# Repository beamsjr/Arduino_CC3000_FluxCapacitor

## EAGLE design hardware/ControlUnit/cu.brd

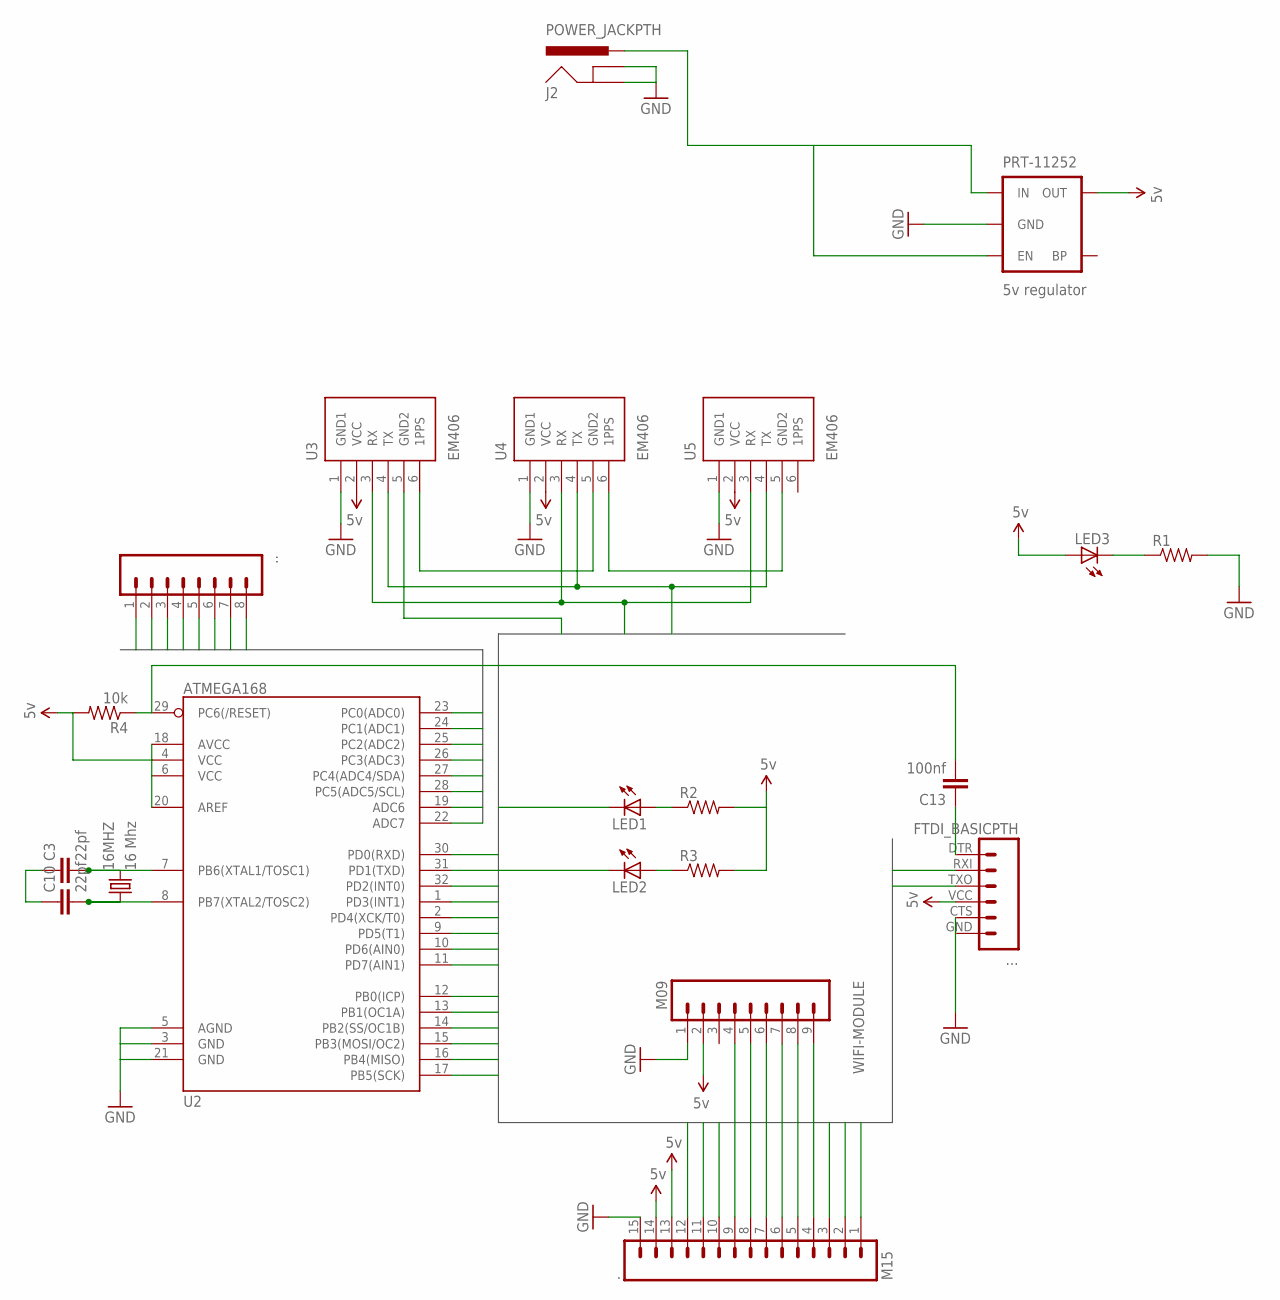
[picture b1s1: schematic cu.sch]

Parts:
16MHZ: 16 Mhz; HC49US
.: M15; 1X15
..: M081X08; 1X08
...: FTDI_BASICPTH; FTDI_BASIC
C3, C10: 22pf; 0805
C13: 100nf; 0805
J2: POWER_JACKPTH; POWER_JACK_PTH
LED1, LED2, LED3: LED1206; LED-1206
PRT-11252: 5v regulator; SOT23-5
R1, R2, R3: RESISTOR0805-RES; 0805
R4: 10k; R0805
U2: ATMEGA168; TQFP32-08
U3, U4, U5: EM406
WIFI-MODULE: M09; 1X09

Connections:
5VCC: ....VCC (4), PRT-11252.5 (OUT), R4.2, U2.4 (VCC), U2.6 (VCC), U2.18 (AVCC), U2.20 (AREF)
A0: ...1, U2.23 (PC0(ADC0))
A1: ...2, U2.24 (PC1(ADC1))
A2: ...3, U2.25 (PC2(ADC2))
A3: ...4, U2.26 (PC3(ADC3))
A4: ...5, U2.27 (PC4(ADC4/SDA))
A5: ...6, U2.28 (PC5(ADC5/SCL))
A6: ...7, U2.19 (ADC6)
A7: ...8, U2.22 (ADC7)
D0: ....TXO (3), LED1.C, U2.30 (PD0(RXD))
D1: ....RXI (2), LED2.C, U2.31 (PD1(TXD))
D2: ..1, U2.32 (PD2(INT0)), WIFI-MODULE.7
D3: ..2, U2.1 (PD3(INT1))
D4: ..3, U2.2 (PD4(XCK/T0))
D5: ..4, U2.9 (PD5(T1)), U3.4 (TX), U4.4 (TX), U5.4 (TX)
D6: ..5, U2.10 (PD6(AIN0)), U3.3 (RX), U4.3 (RX), U5.3 (RX)
D7: ..6, U2.11 (PD7(AIN1)), U3.5 (GND2)
D8: ..7, U2.12 (PB0(ICP))
D9: ..8, U2.13 (PB1(OC1A)), WIFI-MODULE.9
D10: ..9, U2.14 (PB2(SS/OC1B)), WIFI-MODULE.6
D11: ..10, U2.15 (PB3(MOSI/OC2)), WIFI-MODULE.4
D12: ..11, U2.16 (PB4(MISO)), WIFI-MODULE.5
D13: ..12, U2.17 (PB5(SCK)), WIFI-MODULE.8
GND: ..15, ....CTS (5), ....GND (6), J2.GND, J2.GNDBREAK, PRT-11252.2 (GND), R1.2, U2.3 (GND), U2.5 (AGND), U2.21 (GND), U3.1 (GND1), U4.1 (GND1), U5.1 (GND1), WIFI-MODULE.1
unnamed: LED1.A, R2.1
unnamed: LED2.A, R3.1
unnamed: LED3.C, R1.1
unnamed: C13.2, R4.1, U2.29 (PC6(/RESET))
unnamed: 16MHZ.2, C3.2, U2.7 (PB6(XTAL1/TOSC1))
unnamed: 16MHZ.1, C10.2, U2.8 (PB7(XTAL2/TOSC2))
unnamed: U3.6 (1PPS), U4.5 (GND2)
unnamed: U4.6 (1PPS), U5.5 (GND2)
unnamed: J2.PWR, PRT-11252.1 (IN), PRT-11252.3 (EN)
unnamed: ....DTR (1), C13.1
unnamed: C3.1, C10.1
VCC: ..13, ..14, LED3.A, R2.2, R3.2, U3.2 (VCC), U4.2 (VCC), U5.2 (VCC), WIFI-MODULE.2

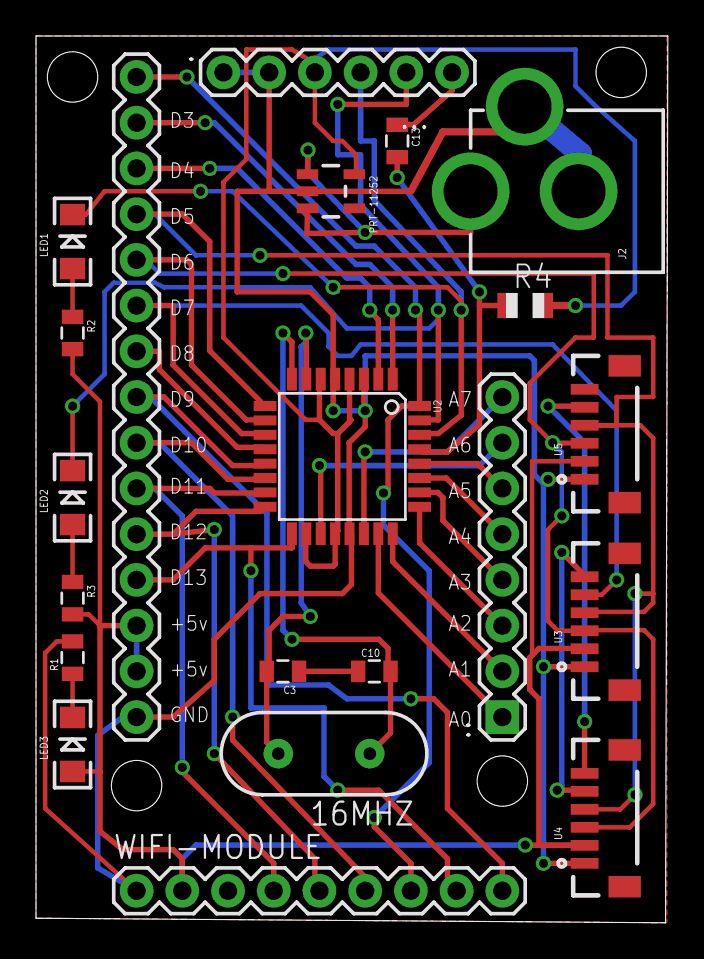
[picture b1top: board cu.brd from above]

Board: 2 copper layers, 35.1 x 49.3 mm, 21 parts (0 on the bottom side), 36 nets.

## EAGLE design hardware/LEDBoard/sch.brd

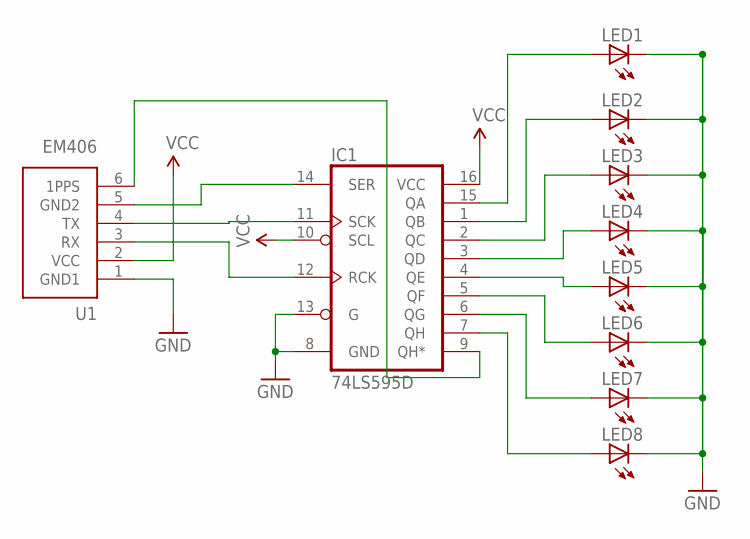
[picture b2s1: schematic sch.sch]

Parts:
IC1: 74LS595D; SO16
LED1, LED2, LED3, LED4, LED5, LED6, LED7, LED8: LED1206; LED-1206
U1: EM406

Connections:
GND: IC1.8 (GND), IC1.13 (G), LED1.C, LED2.C, LED3.C, LED4.C, LED5.C, LED6.C, LED7.C, LED8.C, U1.1 (GND1)
unnamed: IC1.12 (RCK), U1.3 (RX)
unnamed: IC1.9 (QH*), U1.6 (1PPS)
unnamed: IC1.14 (SER), U1.5 (GND2)
unnamed: IC1.15 (QA), LED1.A
unnamed: IC1.11 (SCK), U1.4 (TX)
unnamed: IC1.1 (QB), LED2.A
unnamed: IC1.2 (QC), LED3.A
unnamed: IC1.3 (QD), LED4.A
unnamed: IC1.5 (QF), LED6.A
unnamed: IC1.6 (QG), LED7.A
unnamed: IC1.7 (QH), LED8.A
unnamed: IC1.4 (QE), LED5.A
VCC: IC1.10 (SCL), IC1.16 (VCC), U1.2 (VCC)

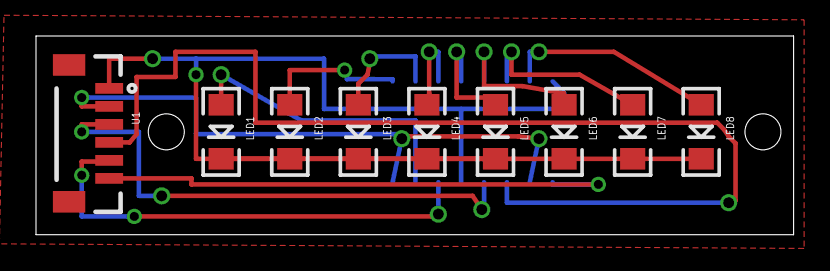
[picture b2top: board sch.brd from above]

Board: 2 copper layers, 42.1 x 11.0 mm, 10 parts (1 on the bottom side), 14 nets.

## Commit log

2014-04-20 Initial Commit
    First sketch with all basics working.
2014-04-21 Removed my ssid
2014-04-24 adding node server
2014-04-24 adding eagle sketches

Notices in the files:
parts and their libraries:
SparkFun-DigitalIC: Licensing: CC v3.0 Share-Alike You are welcome to use this library for commercial purposes.
